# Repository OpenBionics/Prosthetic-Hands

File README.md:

# OpenBionics - Prosthetic Hands
 
Nowadays most prosthetic hands cost dozens of thousands of USD. The OpenBionics initiative (www.openbionics.org) presents a new open-source design for highly functional prosthetic hands. The proposed hands cost less than 200$, weigh less than 300 gr and can be easily fabricated with off-the-shelf materials and rapid prototyping techniques (3D Printing). 

A novel differential mechanism (based on the whiffletree) allows the user to block the motion of each finger independently and facilitates the execution of 144 different grasps with only 1 actuator. The design is based on parametric models of hand anthropometry studies, so it can easily be personalized to specific patients.

## Contents

In this repository you can find:
* Detailed assembly guide for the replication of OpenBionics prosthetic hand 
* Parametric CAD files for personalized design
  * 2D CAD design files for laser cutter 
  * 3D CAD design files for 3D printer
* Breakout board 
* Prosthetic hand kinematics in MATLAB using robotics toolbox
* Arduino software for HerkuleX DRS-0201 servo motor operation
* Archive of various images

## Notes

Please open a [GitHub issue](https://github.com/OpenBionics/Prosthetic-Hands/issues) if you encounter any problem.

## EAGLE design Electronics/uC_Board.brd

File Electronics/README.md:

# Electronic Breakout Board for Prosthetic Hand

We present the development of a breakout board for controlling our prosthetic hand. It is a PCB (printed circuit board) with pin headers to accomodate two different servo motors, such as standard servo and herkulex. It can have both analog inputs (e.g. [EMG](http://www.advancertechnologies.com/p/muscle-sensor-v3.html) signals) and digital inputs (e.g. buttons for [RobotHandExtension](https://github.com/OpenBionics/Robot-Hands/tree/master/CAD/Interfaces/Extension)).
An I2C bus can also be used in order to connect sensors like [takktile] (http://www.takktile.com/) or other servos such as the [openservo](http://openservo.com/). The breakout board also has external pins for development. 

The main microcontroller we currently use is an Arduino Micro Pro, equipped with an ATmega32U4 core. The PCB can be powered by an external power supply or a battery. 

The board is currently under testing. Pictures of the board and its development process can be found below.

# Pinout

The Pin Mapping of the breakout board.

# Board Development

The development of the breakout board was done using the facilities of
the Athens Hackerspace (Thanks!!!). Some photos of the development process and 
final result.

The OpenBionics Electronics Library can be found [here](https://github.com/OpenBionics/Robot-Hands/tree/master/Electronics).

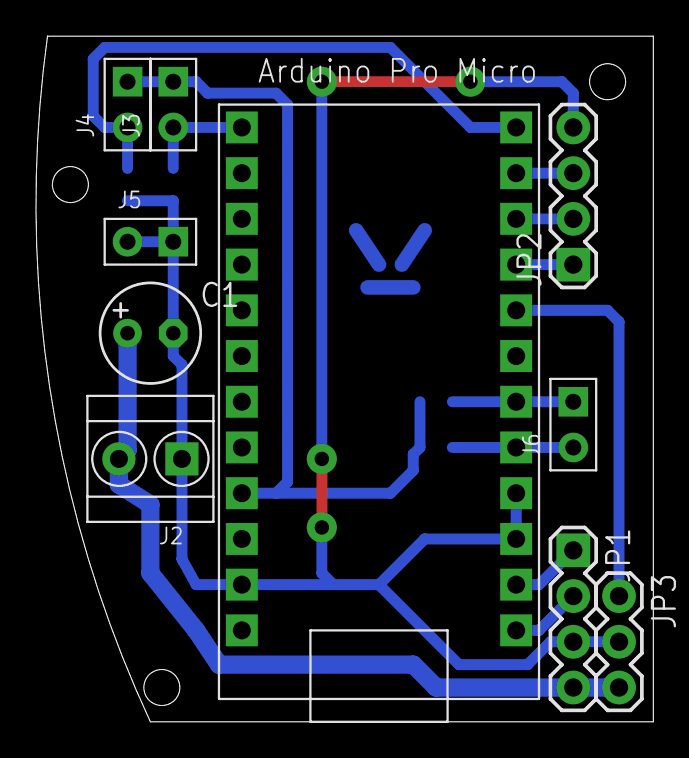
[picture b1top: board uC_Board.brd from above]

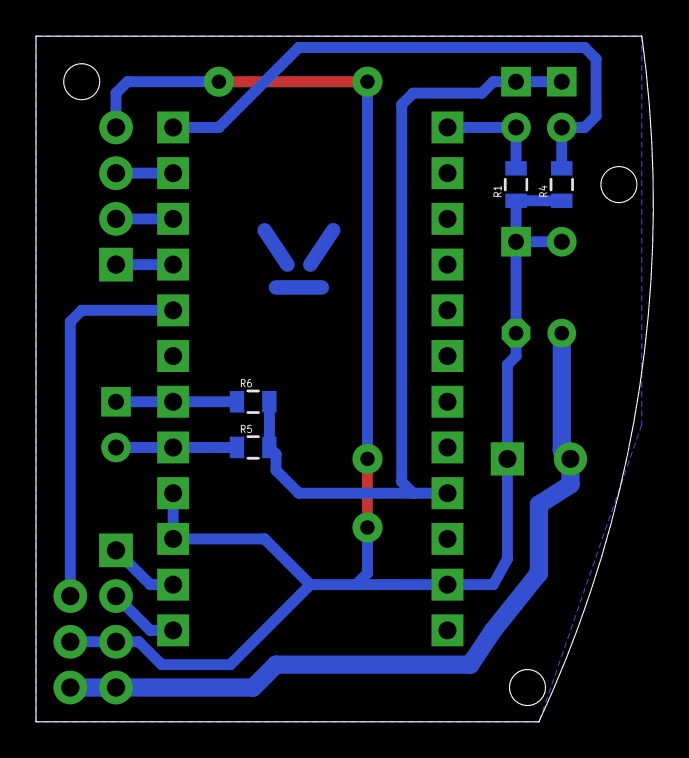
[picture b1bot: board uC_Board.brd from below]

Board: 2 copper layers, 34.3 x 38.1 mm, 14 parts (4 on the bottom side), 13 nets.

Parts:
ARDUINO_MICRO: ARDUINO_PRO_MICROARDUINO_BOARD; ARDUINO_MICRO_PRO
C1: 100u; E2,5-6
J2: SCREW-TERMINAL-2P-3470070P1; 2P-3.5
J3, J5, J6: 2; 2P-2.54-65/35MIL
J4: 3; 2P-2.54-65/35MIL
JP1, JP2: 1X04
JP3: 1X03
R1, R4: 10k; 0805
R5, R6: 0805

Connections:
A7: ARDUINO_MICRO.10, JP2.2
BUTTON1: ARDUINO_MICRO.13, J3.2, R1.2
BUTTON2: ARDUINO_MICRO.12, J4.2, R4.2
GND: ARDUINO_MICRO.3, ARDUINO_MICRO.4, ARDUINO_MICRO.23, C1.-, J2.1, J5.1, J5.2, JP1.3, JP2.4, JP3.2, R1.1, R4.1
IO1: ARDUINO_MICRO.8, JP3.1
IO2: ARDUINO_MICRO.9, JP2.1
IO3: ARDUINO_MICRO.11, JP2.3
RX: ARDUINO_MICRO.2, JP1.1
SCL: ARDUINO_MICRO.6, J6.1, R6.1
SDA: ARDUINO_MICRO.5, J6.2, R5.1
TX: ARDUINO_MICRO.1, JP1.2
VCC: ARDUINO_MICRO.21, J3.1, J4.1, R5.2, R6.2
VS: C1.+, J2.2, JP1.4, JP3.3

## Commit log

2015-03-20 license
2015-03-20 Add new CAD files
2015-03-20 Add new pictures
2015-03-20 Add new CAD rendered pictures
2015-04-10 Update LICENSE.txt
    Remove the non-commercial restriction that are not compatible with open source.
2015-04-16 Create gh-pages branch via GitHub
2015-05-22 Parametric
2015-05-28 Update Assembly
    Resolve conflicts with parameter Finger Width & Palm Radius
2015-05-28 Add Equation to driverBaseFrame
    Equation for change parameter fingerWidth
2015-05-28 Upadate palm to resolve fingerWidth conflicts
    Resolve fingerWidth conflicts, add equation to driverBaseFrame &
    matching of radius
2015-06-26 Update README.md
    Quick guide for personal design & Solidworks
2015-08-15 Add Left & Right Hand
    Left hand was exist.
2015-08-17 Add Human Hand Description photo
2015-08-17 Add Human Hand Description
2015-09-21 Add pictures for new prosthetic board.
2015-09-21 Add eagle files for prosthetic hand board.
2015-09-21 Add .gitignore file.
2015-09-21 Add README file in electronics and new picture for it.
2015-09-21 changes to text
2015-09-21 minor change to title
2015-09-21 Add firmware for arduino and library for Herkulex DRS-0201.
2015-09-21 Add new function setOverloadPWMThreshold and modify the library to work for Atmege32u4.
2015-09-21 Add example for arduino micro and library for Herkulex servo.
2015-09-21 Add README file and picture with interfaces.
2015-09-21 Update the colors in picture.
2015-09-21 Add freecad files for palmup-down parts and pictures for these.
2015-09-21 Update .gitignore file.
2015-10-24 Update and add new palm parts.
2015-10-24 Add new thumb part.
2015-10-24 Add new custom flange part.
2015-10-24 Add parts for buttons.
2015-10-24 Add 3D Design
2015-10-24 Add readme file and new pictures in freecad designs.
2015-10-24 Update button parts.
2015-10-24 Update README.md
    Proofreading!
2015-10-24 Temporarily Delete
2015-10-24 Same button with 2D Design
    Rendered
2015-10-24 Update fingers with bridges
2015-10-24 Update Flange for different interfaces
    New fixing type with palm
2015-10-24 Update palm for 3d Printing
2015-10-24 Add assembly stages
2015-10-24 Fix parametering bugs
2015-10-24 Add new servo base and pulley for Hekrulex DRS 201
2015-10-24 Add 3d printed thumb and different stages of assembly
2015-10-24 Same design with 2D
2015-10-24 3d printed assembly
    Fully Rendered
2015-10-25 Add body harness sources and readme file.
2015-10-25 Repair readme file. Wrong src url for pictures.
2015-10-25 Repair the readme file. Change the position of 1st picture.
2015-10-25 Rephrasing
    Proofreading and rephrasing!
2015-10-25 Discussing the background
    Added some discussion regarding the related work and rephrased some parts.
2015-10-25 Fixed typos
    Fixed typos
2015-10-25 Add new picture and update readme file.
2015-10-25 Repair wrong src url for picture in readme.
2015-10-26 Add readme and pictures for HDM design.
2015-10-26 Rephrased the description
    Rephrased the description and added more information and references.
2015-10-26 Update readme file.
2015-10-26 Add source files and stl for HDM design.
2015-10-26 Add missing stl and source files to HDM design.
2015-10-26 Add Readme for 2D Design
2015-10-26 Add 2D Design model photo
2015-10-26 Update 2D Readme
2015-10-26 Update 3D Readme
2015-10-26 Add photos of 2D and 3D model
2015-10-26 Edit figures
2015-10-26 Add Readme for 3D printed parts
2015-10-26 Add Readme for Laser Cutting files
2015-10-26 Move files
2015-10-26 Update 3D parts Readme
2015-10-26 Update laser Readme
2015-10-26 Add figures
2015-10-26 Add Assembly guide and update .gitignore. We couldn't resolved the conflict with 3dPrinted branch.
2015-10-26 Fix wrong url.
2015-10-26 Fix again wrong url in readme.
2015-10-26 Fix src url in readme file.
2016-02-11 Minor fix (proposal)
2016-02-11 Little fix (proposal)
2016-02-29 Add Kinematics of Prosthesis
2016-10-26 Added tolerances
2016-10-26 Added parameters for tolerances
2016-10-26 Create left hand folder
2016-10-27 Rearranged files for Left hand
2016-10-27 Add right hand
2016-11-05 Added equations so as to take into account the tolerances of different 3D Printers
2016-11-05 Added equations to some parts so as to take into account the tolerances of different 3D Printers
2016-11-05 Update gitignore
2016-11-10 Modified Thumbs.db
2016-11-23 Add tube driver
2016-11-25 Remove old 3D printed files
2016-11-25 Add new 3D printed files for left hand
2016-11-25 Add new 3D printed files for right hand
2017-05-10 Add contents and a note in ReadMe
2017-05-10 Update .gitignore for ROS, MATLAB, and LaTeX
2017-05-11 Fix bug in right hand
2017-05-11 Fix bug in left hand
2018-02-10 Update axes limits

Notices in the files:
parts and their libraries:
SparkFun-Connectors: Licensing: Creative Commons ShareAlike 4.0 International - https://creativecommons.org/licenses/by-sa/4.0
